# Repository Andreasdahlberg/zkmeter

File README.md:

# ZK-meter

ZK-meter is a Zigbee HAN-module for Kamstrup Omnipower electricity meters.

## Features

 * No external power supply needed
 * Fits inside Kamstrump HAN-module casing
 * Supports Zigbee 3.0

## Getting started

### Assembly

1. Open the HAN-Module casing:
    * Use a small screwdriver to release the two clips located on both sides of the HAN-module casing.
    * Gently pull the top cover off to expose the interior.

1. Replace the PCB:
    * Remove the original PCB from its position.
    * Insert the ZK-meter PCB in the same location. Ensure that it fits precisely as the original PCB did.

1. Secure the Top Cover:
    * Place the top cover back onto the HAN-module casing.
    * Press down to secure the top cover in place.

### Installation

1. Insert the HAN-Module:
    * Identify the HAN-port on your meter. It is typically positioned above the display.
    * Carefully insert the HAN-module into the HAN-port.
    * Wait for the LED next to the pairing button to illuminate.

1. Activate Pairing Mode:
    * Press and hold the pairing button on the HAN-module.
    * Keep holding until the LED flashes, indicating that the device is now in pairing mode.

## Troubleshooting

## Development

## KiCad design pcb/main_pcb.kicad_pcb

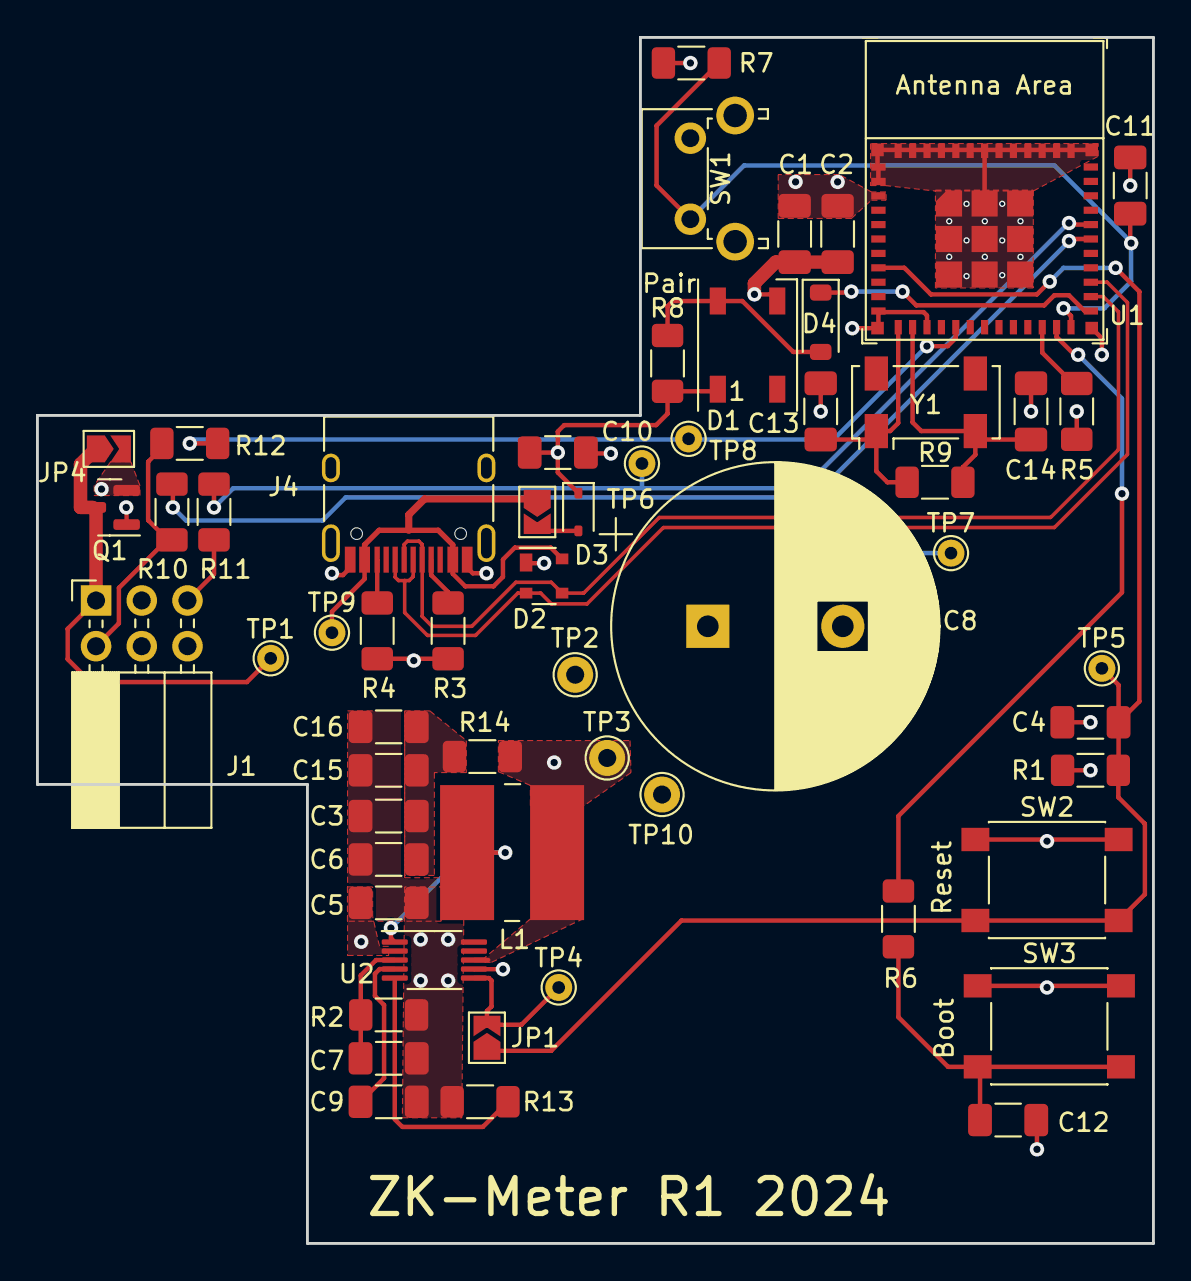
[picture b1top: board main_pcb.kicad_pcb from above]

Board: 4 copper layers, 62.0 x 67.0 mm, 57 parts (0 on the bottom side), 30 nets.

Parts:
C1, C12: 0.1uF; C_1206_3216Metric_Pad1.33x1.80mm_HandSolder
C2, C10: 10uF; C_1206_3216Metric_Pad1.33x1.80mm_HandSolder
C3, C6, C15, C16: 4.7uF; C_1206_3216Metric_Pad1.33x1.80mm_HandSolder
C4, C5, C7, C11: 1uF; C_1206_3216Metric_Pad1.33x1.80mm_HandSolder
C8: 1F; CP_Radial_D18.0mm_P7.50mm
C9: 82nF; C_1206_3216Metric_Pad1.33x1.80mm_HandSolder
C13, C14: 12pF; C_1206_3216Metric_Pad1.33x1.80mm_HandSolder
D1: WS2812B; LED_WS2812B_PLCC4_5.0x5.0mm_P3.2mm
D2: SP0503BAHT; SOT-143
D3: 1N5819WS; D_SOD-323
D4: 1N4148W; D_SOD-123
J1: Conn_01x06_Socket; PinSocket_2x03_P2.54mm_Horizontal
J4: USB_C_Receptacle_USB2.0; USB_C_Receptacle_HRO_TYPE-C-31-M-12
JP1, JP3: SolderJumper_2_Bridged; SolderJumper-2_P1.3mm_Open_TrianglePad1.0x1.5mm
JP4: SolderJumper_2_Open; SolderJumper-2_P1.3mm_Open_TrianglePad1.0x1.5mm
L1: 56uH; L_Wuerth_WE-PD2-Typ-L
Q1: Si2323DS; SOT-23
R1, R5, R6, R7, R8: 10k; R_1206_3216Metric_Pad1.30x1.75mm_HandSolder
R2: 110k; R_1206_3216Metric_Pad1.30x1.75mm_HandSolder
R3, R4: 5k1; R_1206_3216Metric_Pad1.30x1.75mm_HandSolder
R9: 5.1M; R_1206_3216Metric_Pad1.30x1.75mm_HandSolder
R10, R11, R12: 0; R_1206_3216Metric_Pad1.30x1.75mm_HandSolder
R13: 59k; R_1206_3216Metric_Pad1.30x1.75mm_HandSolder
R14: 1.1; R_1206_3216Metric_Pad1.30x1.75mm_HandSolder
SW1: Pair; SW_Tactile_SPST_Angled_PTS645Vx31-2LFS
SW2: Reset; SW_SPST_PTS645
SW3: Boot; SW_SPST_PTS645
TP1: VIN; TestPoint_THTPad_D1.5mm_Drill0.7mm
TP2: VDD; TestPoint_THTPad_D2.0mm_Drill1.0mm
TP3: +3.3V; TestPoint_THTPad_D2.0mm_Drill1.0mm
TP4: PGOOD; TestPoint_THTPad_D1.5mm_Drill0.7mm
TP5: EN; TestPoint_THTPad_D1.5mm_Drill0.7mm
TP6: RXD; TestPoint_THTPad_D1.5mm_Drill0.7mm
TP7: TXD; TestPoint_THTPad_D1.5mm_Drill0.7mm
TP8: DATA_IN; TestPoint_THTPad_D1.5mm_Drill0.7mm
TP9: VBUS; TestPoint_THTPad_D1.5mm_Drill0.7mm
TP10: GND; TestPoint_THTPad_D2.0mm_Drill1.0mm
U1: ESP32-H2-MINI-1
U2: LM5165Y; VSSOP-10_3x3mm_P0.5mm
Y1: 32.768KHz; Crystal_SMD_Abracon_ABS25-4Pin_8.0x3.8mm

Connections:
+3.3V: C1.1, C2.1, C8.1, L1.2, R1.1, R5.2, R14.1, SW1.2, TP3.1, U1.3 (3V3), U2.8 (VOUT)
/D+: D2.2 (K), J4.A6 (D+), J4.B6 (D+), U1.27 (GPIO27/FSPICS5/USB_D+)
/D-: D2.3 (K), J4.A7 (D-), J4.B7 (D-), U1.26 (GPIO26/FSPICS4/USB_D-)
/DATA_IN: R12.2, TP8.1, U1.16 (GPIO12)
/EN: C4.1, JP1.1 (A), R1.2, SW2.2, TP5.1, U1.8 (EN)
/LED: D4.1 (K), U1.25 (GPIO25/FSPICS3)
/PAIR: C11.1, R7.2, SW1.1, U1.24 (GPIO22)
/RXD: R11.2, TP6.1, U1.31 (GPIO24/FSPICS2/U0TXD)
/TXD: R10.2, TP7.1, U1.30 (GPIO23/FSPICS1/U0RXD)
GND: C1.2, C2.2, C3.2, C4.2, C5.2, C6.2, C7.2, C8.2, C9.2, C10.2, C11.2, C12.2, C13.2, C14.2, C15.2, C16.2, D1.3 (VSS), D2.1 (A), J1.6, J4.A1 (GND), J4.A12 (GND), J4.B1 (GND), J4.B12 (GND), Q1.1 (G), R2.2, R3.2, R4.2, R7.1, R13.2, SW2.1, SW3.1, TP10.1, U1.1 (GND), U1.2 (GND), U1.11 (GND), U1.14 (GND), U1.36 (GND), U1.37 (GND), U1.38 (GND), U1.39 (GND), U1.40 (GND), U1.41 (GND), U1.42 (GND), U1.43 (GND), U1.44 (GND), U1.45 (GND), U1.46 (GND), U1.47 (GND), U1.48 (GND), U1.49 (GND), U1.50 (GND), U1.51 (GND), U1.52 (GND), U1.53 (GND), U2.10 (GND)
unnamed: C12.1, R6.2, SW3.2
unnamed: C3.1, C6.1, C15.1, C16.1, R14.2
unnamed: D1.4 (DIN), D4.2 (A), R8.1
unnamed: D3.2 (A), JP3.2 (B)
unnamed: J1.1, JP4.1 (A), Q1.3 (D), TP1.1
unnamed: J1.2, R10.1, R12.1
unnamed: J1.5, R11.1
unnamed: J4.A5 (CC1), R3.1
unnamed: J4.B5 (CC2), R4.1
unnamed: JP1.2 (B), TP4.1, U2.6 (PGOOD)
unnamed: R5.1, U1.22 (GPIO8)
unnamed: R6.1, U1.23 (GPIO9)
unnamed: C13.1, R9.1, U1.12 (GPIO13/XTAL_32K_P), Y1.1
unnamed: C14.1, R9.2, U1.13 (GPIO14/XTAL_32K_N), Y1.2
unnamed: C7.1, R2.1, U2.3 (ILIM)
unnamed: R13.1, U2.5 (RT)
unnamed: C9.1, U2.4 (SS)
unnamed: L1.1, U2.1 (SW)
VBUS: D2.4 (K), J4.A4 (VBUS), J4.A9 (VBUS), J4.B4 (VBUS), J4.B9 (VBUS), JP3.1 (A), TP9.1
VDD: C5.1, C10.1, D1.1 (VDD), D3.1 (K), JP4.2 (B), Q1.2 (S), R8.2, TP2.1, U2.2 (VIN), U2.7 (EN)

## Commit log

2024-02-12 Update kibot.yml
    Use container with Kicad 7.
2024-02-15 Add optional soft start capacitor to power circuit
2024-02-15 Add JTAG header
2024-02-15 Add FTDI header
2024-02-15 Update gitignore
2024-02-15 Add USB-C receptacle
2024-02-15 Add boot selection circuit
2024-02-15 Add ESD protection to USB data lines
2024-02-16 Improve USB circuit
    Add reverse voltage protection and VBUS capacitor.
2024-02-19 Add reverse current protection to HAN-interface
2024-02-19 Replace FTDI power pin jumper with solder bridge
2024-02-19 Add pair button circuit
2024-02-19 Add capacitor to boot switch
2024-02-19 Add status LED circuit
2024-02-19 Add RTC crystal circuit
2024-02-19 Add GND connection to ESP32-H2
2024-02-19 Remove FTDI connector
2024-02-19 Add HAN interface connections to ESP32
2024-02-20 Add keep out areas to PCB
2024-02-20 Add blender output to kibot workflow
2024-02-20 Only render one frame using Blender
2024-02-20 Remove JTAG connector
    Planning on using the built in JTAG via USB.
2024-02-20 Change to 4 layer PCB
2024-02-21 Increase blender 3d-render quality
2024-02-21 Remove redundant capacitor from reset circuit
2024-02-21 Label switches properly
2024-02-21 First rough PCB layout
2024-02-27 Update power supply circuit
    Use values recomended by TI webench power designer.
2024-02-28 Improve PCB layout
2024-03-07 Update PCB layout
2024-03-12 Add custom DRC rules
2024-03-12 Fix DRC errors
2024-03-12 Adjust designator positions
2024-03-13 Add test points
2024-03-13 Increase copper fill free area around the antenna
2024-03-13 Improve connection between 3.3 vreg and 3.3 power plane
2024-03-13 Fix incorrect thermal reliefs
2024-03-13 Add GND test point
